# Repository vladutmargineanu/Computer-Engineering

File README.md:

# Computer-Engineering
Laboratories for the Computer Engineering course @ ACS, UPB 2020

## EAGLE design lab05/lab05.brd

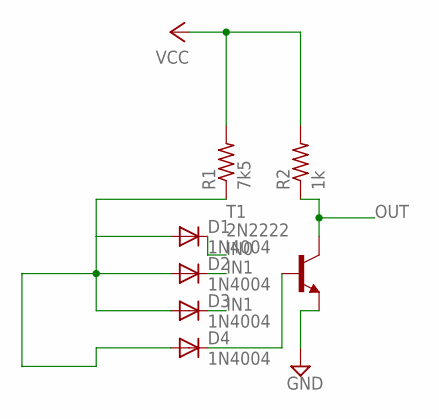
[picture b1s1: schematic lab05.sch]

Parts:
D1, D2, D3, D4: 1N4004; DO41-10
R1: 7k5; 0204/5
R2: 1k; 0204/5
T1: 2N2222; TO92-EBC-OVAL

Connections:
GND: T1.E
IN0: D1.C
IN1: D2.C
unnamed: D1.A, D2.A, D3.A, D4.A, R1.1
unnamed: D4.C, T1.B
OUT: R2.1, T1.C
VCC: R1.2, R2.2

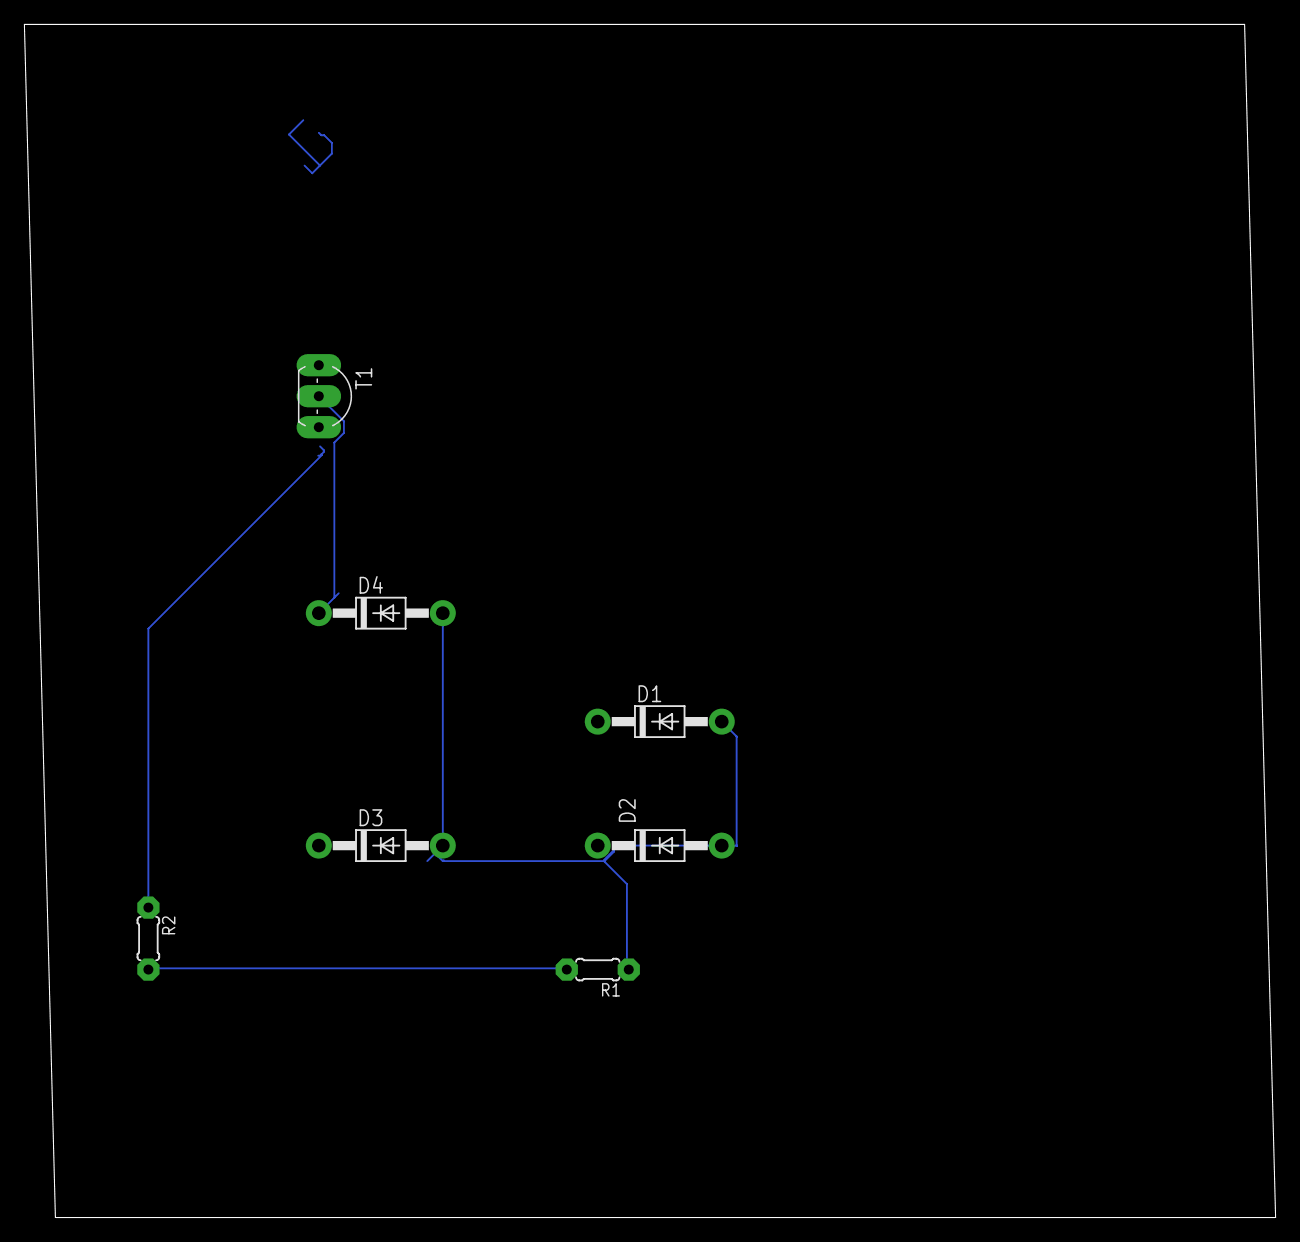
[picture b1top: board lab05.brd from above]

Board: 2 copper layers, 102.5 x 97.8 mm, 7 parts (0 on the bottom side), 4 nets.

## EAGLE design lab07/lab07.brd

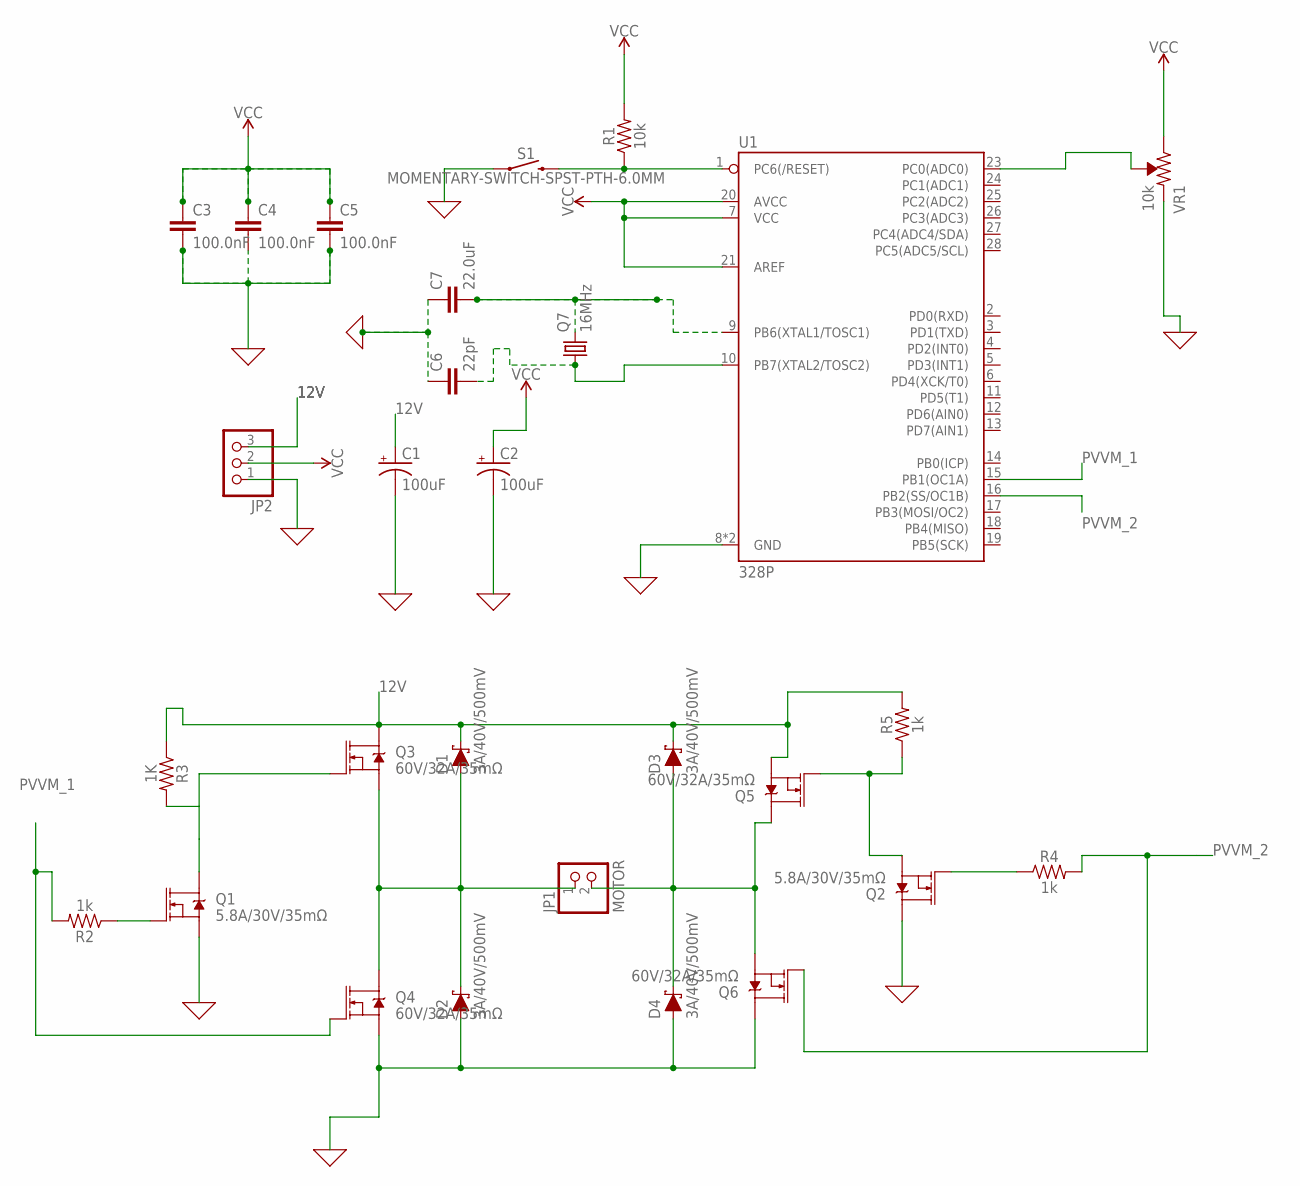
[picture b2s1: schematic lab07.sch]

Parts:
C1, C2: 100uF; CPOL-RADIAL-2.5MM-5MM
C3, C4, C5: 100.0nF; 0805
C6: 22pF; 0805
C7: 22.0uF; 0805
D1, D2, D3, D4: 3A/40V/500mV; SMA-DIODE
JP1: MOTOR; 1X02
JP2: PINHD-1X3; 1X03
Q1, Q2: 5.8A/30V/35mΩ; SOT23-3
Q3, Q4, Q5, Q6: 60V/32A/35mΩ; TO220V
Q7: 16MHz; HC49/S
R1: 10k; 1210
R2, R4, R5: 1k; 1210
R3: 1K; 1210
S1: MOMENTARY-SWITCH-SPST-PTH-6.0MM; TACTILE_SWITCH_PTH_6.0MM
U1: 328P; DIP28
VR1: 10k; TRIMPOT-PTH-3386U

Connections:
0: C1.2 (-), C2.2 (-), C3.2, C4.2, C5.2, C6.1, C7.1, D2.A, D4.A, JP2.1, Q1.2 (S), Q2.3 (D), Q4.3 (S), Q6.2 (D), S1.1, U1.8 (GND), U1.22 (GND), VR1.1 (CCW)
12V: C1.1 (+), D1.C, D3.C, JP2.3, Q3.2 (D), Q5.3 (S), R3.1, R5.2
unnamed: U1.23 (PC0(ADC0)), VR1.2 (WIPER)
unnamed: D1.A, D2.C, JP1.1, Q3.3 (S), Q4.2 (D)
unnamed: C7.2, Q7.2, U1.9 (PB6(XTAL1/TOSC1))
unnamed: C6.2, Q7.1, U1.10 (PB7(XTAL2/TOSC2))
unnamed: R1.1, S1.3 (2), U1.1 (PC6(/RESET))
unnamed: Q1.1 (G), R2.1
unnamed: Q1.3 (D), Q3.1 (G), R3.2
unnamed: Q2.2 (S), Q5.1 (G), R5.1
unnamed: D3.A, D4.C, JP1.2, Q5.2 (D), Q6.3 (S)
unnamed: Q2.1 (G), R4.1
PVVM_1: Q4.1 (G), R2.2, U1.15 (PB1(OC1A))
PVVM_2: Q6.1 (G), R4.2, U1.16 (PB2(SS/OC1B))
VCC: C2.1 (+), C3.1, C4.1, C5.1, JP2.2, R1.2, U1.7 (VCC), U1.20 (AVCC), U1.21 (AREF), VR1.3 (CW)

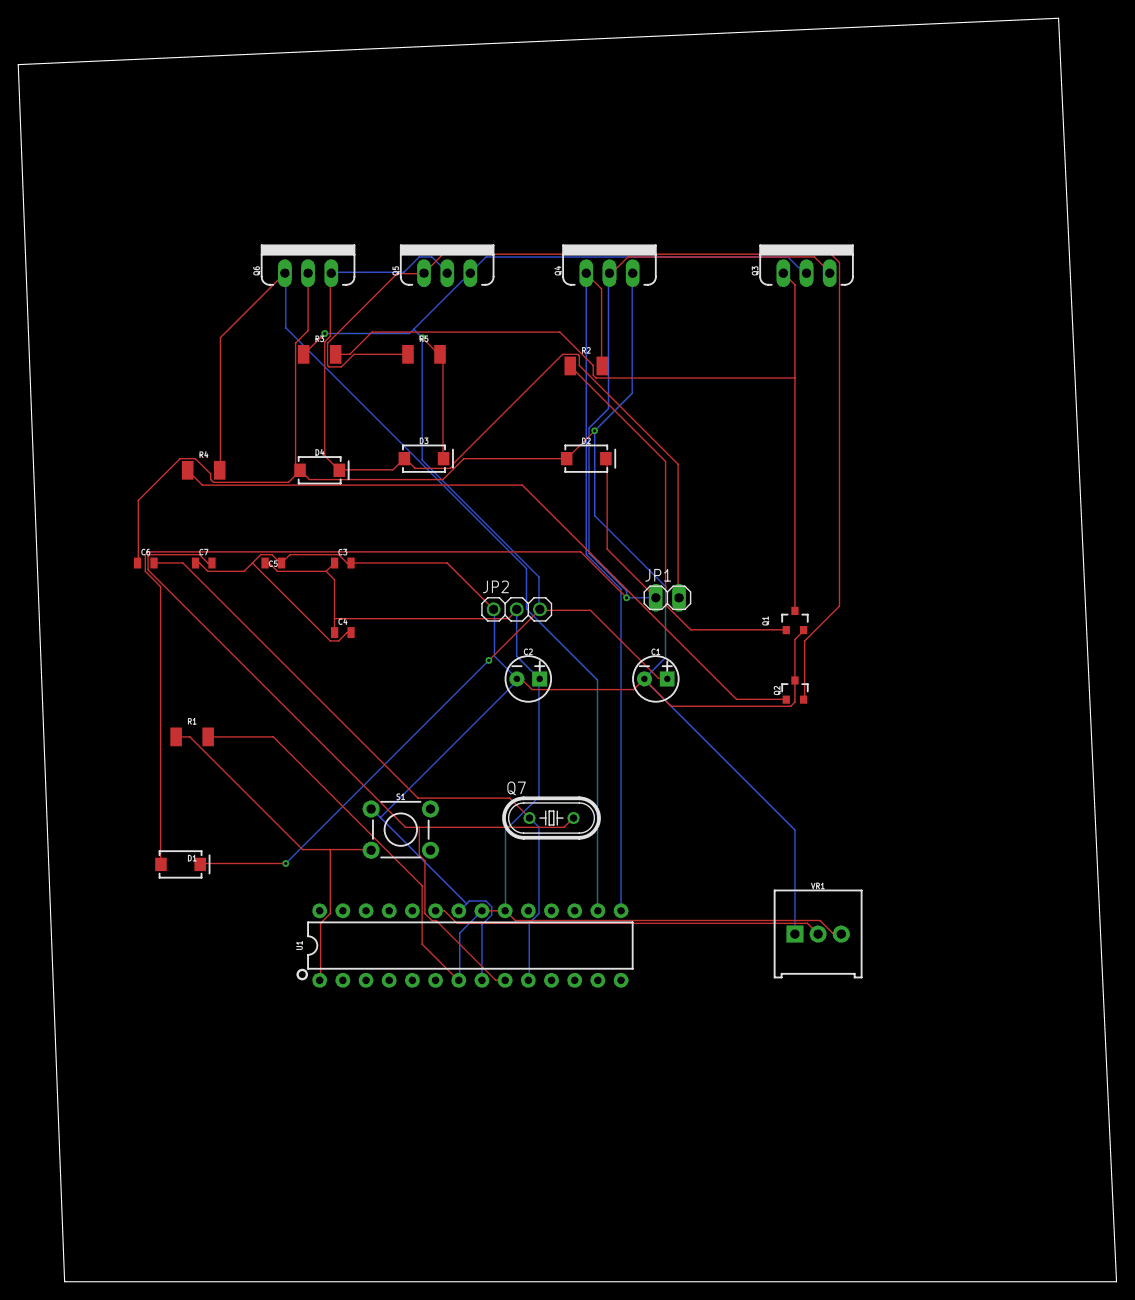
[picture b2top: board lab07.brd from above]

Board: 2 copper layers, 120.3 x 138.4 mm, 28 parts (0 on the bottom side), 15 nets.

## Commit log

2021-04-20 laboratories eagle
2021-04-20 lab 04

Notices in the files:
parts and their libraries:
SparkFun-Capacitors: Licensing: Creative Commons ShareAlike 4.0 International - https://creativecommons.org/licenses/by-sa/4.0
